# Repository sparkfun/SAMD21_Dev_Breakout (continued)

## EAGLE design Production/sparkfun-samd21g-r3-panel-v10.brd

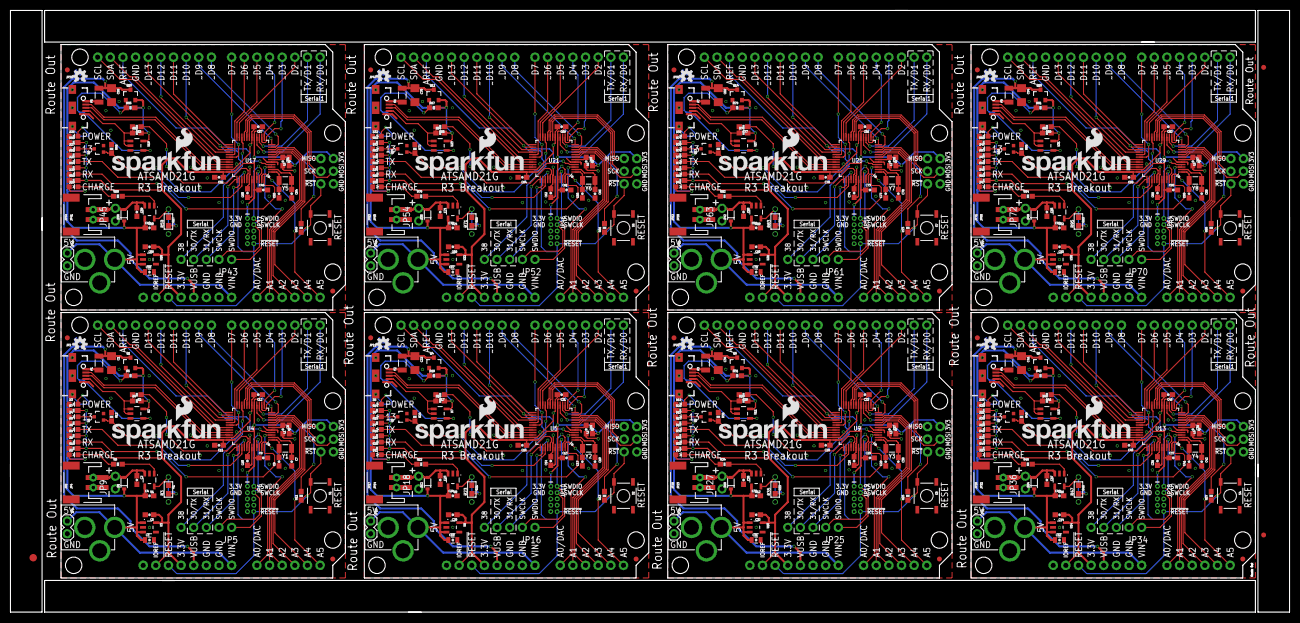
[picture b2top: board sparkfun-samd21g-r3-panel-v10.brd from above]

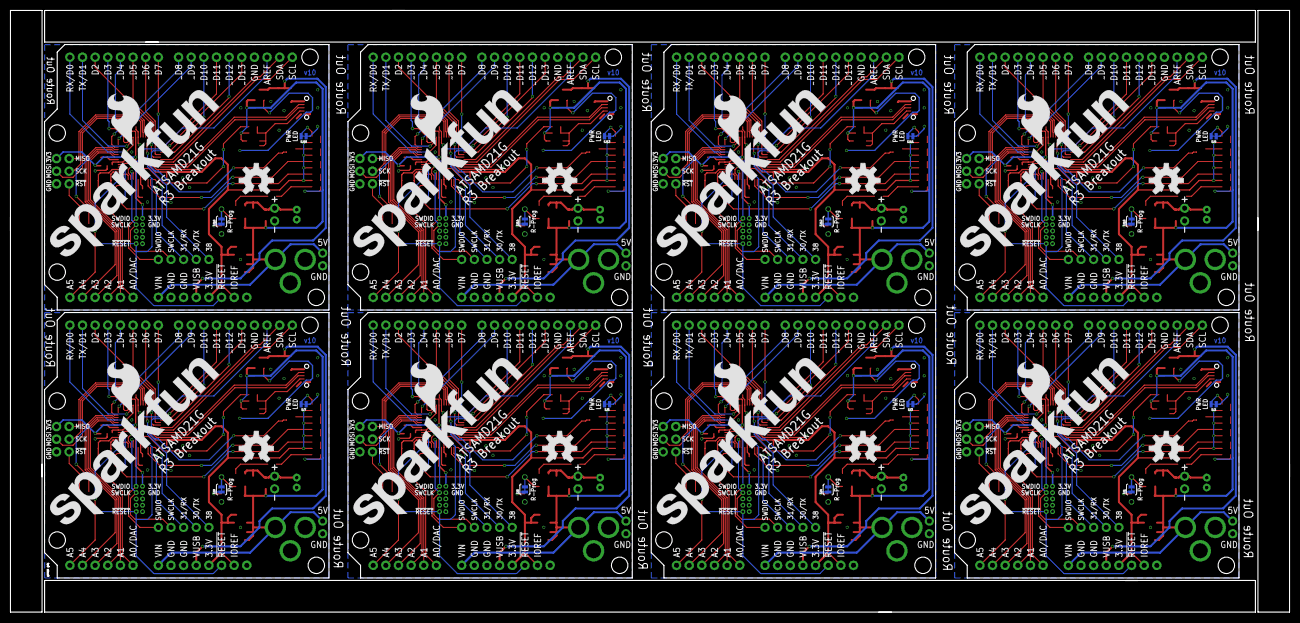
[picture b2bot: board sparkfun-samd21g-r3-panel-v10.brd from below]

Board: 2 copper layers, 257.0 x 120.9 mm, 491 parts (32 on the bottom side), 472 nets.

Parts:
C1, C22, C34, C46, C58, C70, C82, C94: 2.2UF; 1206
C2, C4, C23, C24, C35, C36, C47, C48, C59, C60, C71, C72, C83, C84, C95, C96: 4.7uF; 0603-CAP
C3, C19, C31, C43, C55, C67, C79, C91: 1.0uF; 0805-CAP
C5, C20, C32, C44, C56, C68, C80, C92: 2.2uF; 0603-CAP
C6, C8, C10, C11, C12, C13, C14, C15, C16, C21, C25, C26, C27, C28, C33, C37, C38, C39, C40, C45, C49, C50, C51, C52, C57, C61, C62, C63, C64, C69, C73, C74, C75, C76, C81, C85, C86, C87, C88, C93: 0.1uF; 0603-CAP
C7, C9, C17, C18, C29, C30, C41, C42, C53, C54, C65, C66, C77, C78, C89, C90: 15pF; 0603-CAP
D1, D12, D18, D24, D30, D36, D42, D48: BAT20J; SOD-323
D2, D3, D8, D11, D14, D17, D20, D23, D26, D29, D32, D35, D38, D41, D44, D47: RED; LED-0603
D4, D9, D15, D21, D27, D33, D39, D45: BLUE; LED-0603
D5, D7, D13, D19, D25, D31, D37, D43: GREEN; LED-0603
D6, D10, D16, D22, D28, D34, D40, D46: Yellow; LED-0603
E$1: FIDUCIAL-1.5X3
E$5, E$6: FIDUCIAL-1X2
F1, F2, F3, F4, F5, F6, F7, F8: 500mA; PTC-1206
FID1, FID2, FID3, FID4, FID5, FID6, FID7, FID8, FID9, FID10, FID11, FID12, FID13, FID14, FID15, FID16: FIDUCIAL1X2; FIDUCIAL-1X2
JP1, JP15, JP24, JP33, JP42, JP51, JP60, JP69: 1X02
JP2, JP11, JP20, JP29, JP38, JP47, JP56, JP65: USB-AB-MICRO-SMD_V03
JP3, JP13, JP22, JP31, JP40, JP49, JP58, JP67: POWER_JACKPTH; POWER_JACK_PTH
JP4, JP14, JP23, JP32, JP41, JP50, JP59, JP68: JST-2-SMD
JP5, JP16, JP25, JP34, JP43, JP52, JP61, JP70: 1X05_NO_SILK
JP6, JP10, JP19, JP28, JP37, JP46, JP55, JP64: CORTEX_DEBUGPTH; 2X5-PTH-1.27MM
JP7, JP12, JP21, JP30, JP39, JP48, JP57, JP66: ARDUINO_R3NO_HOLES; ARDUINO_R3_NO_HOLES
JP8, JP17, JP26, JP35, JP44, JP53, JP62, JP71: JST-2-PTH-NS
JP9, JP18, JP27, JP36, JP45, JP54, JP63, JP72: 1X02_NO_SILK
L1, L2, L3, L4, L5, L6, L7, L8: FB - 30Ohm; 0603
LOGO1, LOGO6, LOGO10, LOGO14, LOGO18, LOGO22, LOGO26, LOGO30: SFE_LOGO_NAME_FLAME.2_INCH; SFE_LOGO_NAME_FLAME_.2
LOGO2, LOGO7, LOGO11, LOGO15, LOGO19, LOGO23, LOGO27, LOGO31: SFE_LOGO_NAME_FLAME.4_INCH; SFE_LOGO_NAME_FLAME_.4
LOGO3, LOGO5, LOGO9, LOGO13, LOGO17, LOGO21, LOGO25, LOGO29: OSHW-LOGOS; OSHW-LOGO-S
LOGO4, LOGO8, LOGO12, LOGO16, LOGO20, LOGO24, LOGO28, LOGO32: OSHW-LOGOL; OSHW-LOGO-L
Q1, Q4, Q6, Q8, Q10, Q12, Q14, Q16: 2.5A/30V; SOT23-3
Q2, Q3, Q5, Q7, Q9, Q11, Q13, Q15: 2N7002PW; SOT323
R1, R21, R33, R45, R57, R69, R81, R93: 3.9K; 0603
R2, R6, R7, R8, R9, R10, R14, R15, R17, R18, R20, R22, R26, R27, R29, R30, R32, R34, R38, R39, R41, R42, R44, R46, R50, R51, R53, R54, R56, R58, R62, R63, R65, R66, R68, R70, R74, R75, R77, R78, R80, R82, R86, R87, R89, R90, R92, R94: 330; 0603-RES
R3, R23, R35, R47, R59, R71, R83, R95: PROG; 1/6W-RES
R4, R12, R16, R24, R28, R36, R40, R48, R52, R60, R64, R72, R76, R84, R88, R96: 100k; 0603-RES
R5, R19, R31, R43, R55, R67, R79, R91: 47K; 0603-RES
R11, R13, R25, R37, R49, R61, R73, R85: 10K; 0603-RES
S1, S2, S3, S4, S5, S6, S7, S8: RESET; TACTILE-SWITCH-SMD
SJ1, SJ4, SJ6, SJ8, SJ10, SJ12, SJ14, SJ16: R-prog; PAD-JUMPER-2-NC_BY_TRACE_YES_SILK
SJ2, SJ3, SJ5, SJ7, SJ9, SJ11, SJ13, SJ15: PWR-LED; PAD-JUMPER-2-NC_BY_TRACE_NO_SILK
STANDOFF1, STANDOFF2, STANDOFF3, STANDOFF4, STANDOFF5, STANDOFF6, STANDOFF7, STANDOFF8, STANDOFF9, STANDOFF10, STANDOFF11, STANDOFF12, STANDOFF13, STANDOFF14, STANDOFF15, STANDOFF16, STANDOFF17, STANDOFF18, STANDOFF19, STANDOFF20, STANDOFF21, STANDOFF22, STANDOFF23, STANDOFF24, STANDOFF25, STANDOFF26, STANDOFF27, STANDOFF28, STANDOFF29, STANDOFF30, STANDOFF31, STANDOFF32: STAND-OFF
U1, U8, U12, U16, U20, U24, U28, U32: MCP73831; SOT23-5
U2, U7, U11, U15, U19, U23, U27, U31: 74AHC1G125; SOT23-5
U3, U6, U10, U14, U18, U22, U26, U30: 3.3V; SOT23-5
U4, U5, U9, U13, U17, U21, U25, U29: ATSAMD21G-A; TQFP-48
Y1, Y2, Y3, Y4, Y5, Y6, Y7, Y8: 32.768kHz; CRYSTAL-SMD-3.2X1.5MM

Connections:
3.3V: C5.1, C8.1, C11.1, C12.1, JP6.1, JP7.3.3V, JP7.IOREF, JP7.VCC, L1.1, R7.2, R8.2, R9.2, R10.2, R11.2, U3.5, U4.17, U4.36, U4.44
3.3V1: C13.1, C16.1, C20.1, C21.1, JP10.1, JP12.3.3V, JP12.IOREF, JP12.VCC, L2.1, R13.2, R14.2, R15.2, R18.2, R20.2, U5.17, U5.36, U5.44, U6.5
3.3V2: C25.1, C28.1, C32.1, C33.1, JP19.1, JP21.3.3V, JP21.IOREF, JP21.VCC, L3.1, R25.2, R26.2, R27.2, R30.2, R32.2, U9.17, U9.36, U9.44, U10.5
3.3V3: C37.1, C40.1, C44.1, C45.1, JP28.1, JP30.3.3V, JP30.IOREF, JP30.VCC, L4.1, R37.2, R38.2, R39.2, R42.2, R44.2, U13.17, U13.36, U13.44, U14.5
3.3V4: C49.1, C52.1, C56.1, C57.1, JP37.1, JP39.3.3V, JP39.IOREF, JP39.VCC, L5.1, R49.2, R50.2, R51.2, R54.2, R56.2, U17.17, U17.36, U17.44, U18.5
3.3V5: C61.1, C64.1, C68.1, C69.1, JP46.1, JP48.3.3V, JP48.IOREF, JP48.VCC, L6.1, R61.2, R62.2, R63.2, R66.2, R68.2, U21.17, U21.36, U21.44, U22.5
3.3V6: C73.1, C76.1, C80.1, C81.1, JP55.1, JP57.3.3V, JP57.IOREF, JP57.VCC, L7.1, R73.2, R74.2, R75.2, R78.2, R80.2, U25.17, U25.36, U25.44, U26.5
3.3V7: C85.1, C88.1, C92.1, C93.1, JP64.1, JP66.3.3V, JP66.IOREF, JP66.VCC, L8.1, R85.2, R86.2, R87.2, R90.2, R92.2, U29.17, U29.36, U29.44, U30.5
!RESET: JP6.10, JP7.RESET@1, JP7.RESET@2, R11.1, S1.3, U4.40
!RESET1: JP10.10, JP12.RESET@1, JP12.RESET@2, R13.1, S2.3, U5.40
!RESET2: JP19.10, JP21.RESET@1, JP21.RESET@2, R25.1, S3.3, U9.40
!RESET3: JP28.10, JP30.RESET@1, JP30.RESET@2, R37.1, S4.3, U13.40
!RESET4: JP37.10, JP39.RESET@1, JP39.RESET@2, R49.1, S5.3, U17.40
!RESET5: JP46.10, JP48.RESET@1, JP48.RESET@2, R61.1, S6.3, U21.40
!RESET6: JP55.10, JP57.RESET@1, JP57.RESET@2, R73.1, S7.3, U25.40
!RESET7: JP64.10, JP66.RESET@1, JP66.RESET@2, R85.1, S8.3, U29.40
A0: JP7.A0, U4.3
A1: JP7.A1, U4.7
A2: JP7.A2, U4.8
A3: JP7.A3, U4.9
A4: JP7.A4, U4.10
A5: JP7.A5, U4.47
A6: JP12.A3, U5.9
A7: JP12.A2, U5.8
A8: JP12.A1, U5.7
A9: JP12.A0, U5.3
A10: JP12.A4, U5.10
A11: JP12.A5, U5.47
A12: JP21.A3, U9.9
A13: JP21.A2, U9.8
A14: JP21.A1, U9.7
A15: JP21.A0, U9.3
A16: JP21.A4, U9.10
A17: JP21.A5, U9.47
A18: JP30.A3, U13.9
A19: JP30.A2, U13.8
A20: JP30.A1, U13.7
A21: JP30.A0, U13.3
A22: JP30.A4, U13.10
A23: JP30.A5, U13.47
A24: JP39.A3, U17.9
A25: JP39.A2, U17.8
A26: JP39.A1, U17.7
A27: JP39.A0, U17.3
A28: JP39.A4, U17.10
A29: JP39.A5, U17.47
A30: JP48.A3, U21.9
A31: JP48.A2, U21.8
A32: JP48.A1, U21.7
A33: JP48.A0, U21.3
A34: JP48.A4, U21.10
A35: JP48.A5, U21.47
A36: JP57.A3, U25.9
A37: JP57.A2, U25.8
A38: JP57.A1, U25.7
A39: JP57.A0, U25.3
A40: JP57.A4, U25.10
A41: JP57.A5, U25.47
A42: JP66.A3, U29.9
A43: JP66.A2, U29.8
A44: JP66.A1, U29.7
A45: JP66.A0, U29.3
A46: JP66.A4, U29.10
A47: JP66.A5, U29.47
AREF: JP7.AREF, U4.4
AREF1: JP12.AREF, U5.4
AREF2: JP21.AREF, U9.4
AREF3: JP30.AREF, U13.4
AREF4: JP39.AREF, U17.4
AREF5: JP48.AREF, U21.4
AREF6: JP57.AREF, U25.4
AREF7: JP66.AREF, U29.4
CHG_STAT: R6.2, U1.1
CHG_STAT1: R22.2, U8.1
CHG_STAT2: R34.2, U12.1
CHG_STAT3: R46.2, U16.1
CHG_STAT4: R58.2, U20.1
CHG_STAT5: R70.2, U24.1
CHG_STAT6: R82.2, U28.1
CHG_STAT7: R94.2, U32.1
D0/RXI: JP7.D0, U4.16
D0/RXI1: JP12.D0, U5.16
D0/RXI2: JP21.D0, U9.16
D0/RXI3: JP30.D0, U13.16
D0/RXI4: JP39.D0, U17.16
D0/RXI5: JP48.D0, U21.16
D0/RXI6: JP57.D0, U25.16
D0/RXI7: JP66.D0, U29.16
D1: JP12.D4, U5.13
D1/TXO: JP7.D1, U4.15
D1/TXO1: JP12.D1, U5.15
D1/TXO2: JP21.D1, U9.15
D1/TXO3: JP30.D1, U13.15
D1/TXO4: JP39.D1, U17.15
D1/TXO5: JP48.D1, U21.15
D1/TXO6: JP57.D1, U25.15
D1/TXO7: JP66.D1, U29.15
D2: JP7.D2, U4.23
D3: JP7.D3, U4.14
D4: JP7.D4, U4.13
D5: JP7.D5, U4.24
D6: JP7.D6, U4.29
D7: JP7.D7, U4.30
D8: JP7.D8, U4.11
D9: JP7.D9, U4.12
D10: JP7.D10, U4.27
D11: JP7.D11, U4.25
D12: JP7.D12, U4.28
D13: JP7.D13, Q2.1, R12.2, U4.26
D14: JP12.D3, U5.14
D15: JP12.D2, U5.23
D16: JP12.D5, U5.24
D17: JP12.D6, U5.29
D18: JP12.D7, U5.30
D19: JP12.D8, U5.11
D20: JP12.D9, U5.12
D21: JP12.D12, U5.28
D22: JP12.D11, U5.25
D23: JP12.D10, U5.27
D24: JP12.D13, Q3.1, R24.2, U5.26
D25: JP21.D4, U9.13
D26: JP21.D3, U9.14
D27: JP21.D2, U9.23
D28: JP21.D5, U9.24
D29: JP21.D6, U9.29
D30: JP21.D7, U9.30
D31: JP21.D8, U9.11
D32: JP21.D9, U9.12
D33: JP21.D12, U9.28
D34: JP21.D11, U9.25
D35: JP21.D10, U9.27
D36: JP21.D13, Q5.1, R36.2, U9.26
D37: JP30.D4, U13.13
D38: JP30.D3, U13.14
D39: JP30.D2, U13.23
D40: JP30.D5, U13.24
D41: JP30.D6, U13.29
D42: JP30.D7, U13.30
D43: JP30.D8, U13.11
D44: JP30.D9, U13.12
D45: JP30.D12, U13.28
D46: JP30.D11, U13.25
D47: JP30.D10, U13.27
D48: JP30.D13, Q7.1, R48.2, U13.26
D49: JP39.D4, U17.13
D50: JP39.D3, U17.14
D51: JP39.D2, U17.23
D52: JP39.D5, U17.24
D53: JP39.D6, U17.29
D54: JP39.D7, U17.30
D55: JP39.D8, U17.11
D56: JP39.D9, U17.12
D57: JP39.D12, U17.28
D58: JP39.D11, U17.25
D59: JP39.D10, U17.27
D60: JP39.D13, Q9.1, R60.2, U17.26
D61: JP48.D4, U21.13
D62: JP48.D3, U21.14
D63: JP48.D2, U21.23
D64: JP48.D5, U21.24
D65: JP48.D6, U21.29
D66: JP48.D7, U21.30
D67: JP48.D8, U21.11
D68: JP48.D9, U21.12
D69: JP48.D12, U21.28
D70: JP48.D11, U21.25
D71: JP48.D10, U21.27
D72: JP48.D13, Q11.1, R72.2, U21.26
D73: JP57.D4, U25.13
D74: JP57.D3, U25.14
D75: JP57.D2, U25.23
D76: JP57.D5, U25.24
D77: JP57.D6, U25.29
D78: JP57.D7, U25.30
D79: JP57.D8, U25.11
D80: JP57.D9, U25.12
D81: JP57.D12, U25.28
D82: JP57.D11, U25.25
D83: JP57.D10, U25.27
D84: JP57.D13, Q13.1, R84.2, U25.26
D85: JP66.D4, U29.13
D86: JP66.D3, U29.14
D87: JP66.D2, U29.23
D88: JP66.D5, U29.24
D89: JP66.D6, U29.29
D90: JP66.D7, U29.30
D91: JP66.D8, U29.11
D92: JP66.D9, U29.12
D93: JP66.D12, U29.28
D94: JP66.D11, U29.25
D95: JP66.D10, U29.27
D96: JP66.D13, Q15.1, R96.2, U29.26
GND: C1.2, C2.2, C3.2, C4.2, C5.2, C6.2, C7.2, C8.2, C9.1, C10.2, C11.2, C12.2, JP1.1, JP2.GND1, JP2.SHIELD1, JP2.SHIELD2, JP2.SHIELD3, JP3.GND, JP3.GNDBREAK, JP4.1, JP6.3, JP6.5, JP7.GND@1, JP7.GND@2, JP7.GND@3, JP7.GND@4, JP8.1, JP9.1, Q2.2, R1.1, R3.1, R12.1, S1.1, SJ2.1, U1.2, U2.3, U3.2, U4.5, U4.18, U4.35, U4.42
GND1: C13.2, C14.2, C15.2, C16.2, C17.1, C18.2, C19.2, C20.2, C21.2, C22.2, C23.2, C24.2, JP10.3, JP10.5, JP11.GND1, JP11.SHIELD1, JP11.SHIELD2, JP11.SHIELD3, JP12.GND@1, JP12.GND@2, JP12.GND@3, JP12.GND@4, JP13.GND, JP13.GNDBREAK, JP14.1, JP15.1, JP17.1, JP18.1, Q3.2, R21.1, R23.1, R24.1, S2.1, SJ3.1, U5.5, U5.18, U5.35, U5.42, U6.2, U7.3, U8.2
GND2: C25.2, C26.2, C27.2, C28.2, C29.1, C30.2, C31.2, C32.2, C33.2, C34.2, C35.2, C36.2, JP19.3, JP19.5, JP20.GND1, JP20.SHIELD1, JP20.SHIELD2, JP20.SHIELD3, JP21.GND@1, JP21.GND@2, JP21.GND@3, JP21.GND@4, JP22.GND, JP22.GNDBREAK, JP23.1, JP24.1, JP26.1, JP27.1, Q5.2, R33.1, R35.1, R36.1, S3.1, SJ5.1, U9.5, U9.18, U9.35, U9.42, U10.2, U11.3, U12.2
GND3: C37.2, C38.2, C39.2, C40.2, C41.1, C42.2, C43.2, C44.2, C45.2, C46.2, C47.2, C48.2, JP28.3, JP28.5, JP29.GND1, JP29.SHIELD1, JP29.SHIELD2, JP29.SHIELD3, JP30.GND@1, JP30.GND@2, JP30.GND@3, JP30.GND@4, JP31.GND, JP31.GNDBREAK, JP32.1, JP33.1, JP35.1, JP36.1, Q7.2, R45.1, R47.1, R48.1, S4.1, SJ7.1, U13.5, U13.18, U13.35, U13.42, U14.2, U15.3, U16.2
GND4: C49.2, C50.2, C51.2, C52.2, C53.1, C54.2, C55.2, C56.2, C57.2, C58.2, C59.2, C60.2, JP37.3, JP37.5, JP38.GND1, JP38.SHIELD1, JP38.SHIELD2, JP38.SHIELD3, JP39.GND@1, JP39.GND@2, JP39.GND@3, JP39.GND@4, JP40.GND, JP40.GNDBREAK, JP41.1, JP42.1, JP44.1, JP45.1, Q9.2, R57.1, R59.1, R60.1, S5.1, SJ9.1, U17.5, U17.18, U17.35, U17.42, U18.2, U19.3, U20.2
GND5: C61.2, C62.2, C63.2, C64.2, C65.1, C66.2, C67.2, C68.2, C69.2, C70.2, C71.2, C72.2, JP46.3, JP46.5, JP47.GND1, JP47.SHIELD1, JP47.SHIELD2, JP47.SHIELD3, JP48.GND@1, JP48.GND@2, JP48.GND@3, JP48.GND@4, JP49.GND, JP49.GNDBREAK, JP50.1, JP51.1, JP53.1, JP54.1, Q11.2, R69.1, R71.1, R72.1, S6.1, SJ11.1, U21.5, U21.18, U21.35, U21.42, U22.2, U23.3, U24.2
GND6: C73.2, C74.2, C75.2, C76.2, C77.1, C78.2, C79.2, C80.2, C81.2, C82.2, C83.2, C84.2, JP55.3, JP55.5, JP56.GND1, JP56.SHIELD1, JP56.SHIELD2, JP56.SHIELD3, JP57.GND@1, JP57.GND@2, JP57.GND@3, JP57.GND@4, JP58.GND, JP58.GNDBREAK, JP59.1, JP60.1, JP62.1, JP63.1, Q13.2, R81.1, R83.1, R84.1, S7.1, SJ13.1, U25.5, U25.18, U25.35, U25.42, U26.2, U27.3, U28.2
GND7: C85.2, C86.2, C87.2, C88.2, C89.1, C90.2, C91.2, C92.2, C93.2, C94.2, C95.2, C96.2, JP64.3, JP64.5, JP65.GND1, JP65.SHIELD1, JP65.SHIELD2, JP65.SHIELD3, JP66.GND@1, JP66.GND@2, JP66.GND@3, JP66.GND@4, JP67.GND, JP67.GNDBREAK, JP68.1, JP69.1, JP71.1, JP72.1, Q15.2, R93.1, R95.1, R96.1, S8.1, SJ15.1, U29.5, U29.18, U29.35, U29.42, U30.2, U31.3, U32.2
unnamed: F1.1, JP2.VBUS1
unnamed: C9.2, U4.1, Y1.P$2
unnamed: D4.C, Q2.3
unnamed: C7.1, U4.2, Y1.P$1
unnamed: D3.A, R7.1
unnamed: D4.A, R8.1
unnamed: C17.2, U5.1, Y2.P$2
unnamed: D2.C, R6.1
unnamed: C18.1, U5.2, Y2.P$1
unnamed: D5.A, R9.1
unnamed: D6.A, R10.1
unnamed: D3.C, SJ2.2
unnamed: R1.2, SJ1.1
unnamed: D8.A, R14.1
unnamed: R3.2, SJ1.2, U1.5
unnamed: D9.A, R15.1
unnamed: D9.C, Q3.3
unnamed: F2.1, JP11.VBUS1
unnamed: D7.A, R18.1
unnamed: D10.A, R20.1
unnamed: D8.C, SJ3.2
unnamed: R21.2, SJ4.1
unnamed: R23.2, SJ4.2, U8.5
unnamed: D11.C, R22.1
unnamed: C29.2, U9.1, Y3.P$2
unnamed: C30.1, U9.2, Y3.P$1
unnamed: D14.A, R26.1
unnamed: D15.A, R27.1
unnamed: D15.C, Q5.3
unnamed: F3.1, JP20.VBUS1
unnamed: D13.A, R30.1
unnamed: D16.A, R32.1
unnamed: D14.C, SJ5.2
unnamed: R33.2, SJ6.1
unnamed: R35.2, SJ6.2, U12.5
unnamed: D17.C, R34.1
unnamed: C41.2, U13.1, Y4.P$2
unnamed: C42.1, U13.2, Y4.P$1
unnamed: D20.A, R38.1
unnamed: D21.A, R39.1
unnamed: D21.C, Q7.3
unnamed: F4.1, JP29.VBUS1
unnamed: D19.A, R42.1
unnamed: D22.A, R44.1
unnamed: D20.C, SJ7.2
unnamed: R45.2, SJ8.1
unnamed: R47.2, SJ8.2, U16.5
unnamed: D23.C, R46.1
unnamed: C53.2, U17.1, Y5.P$2
unnamed: C54.1, U17.2, Y5.P$1
unnamed: D26.A, R50.1
unnamed: D27.A, R51.1
unnamed: D27.C, Q9.3
unnamed: F5.1, JP38.VBUS1
unnamed: D25.A, R54.1
unnamed: D28.A, R56.1
unnamed: D26.C, SJ9.2
unnamed: R57.2, SJ10.1
unnamed: R59.2, SJ10.2, U20.5
unnamed: D29.C, R58.1
unnamed: C65.2, U21.1, Y6.P$2
unnamed: C66.1, U21.2, Y6.P$1
unnamed: D32.A, R62.1
unnamed: D33.A, R63.1
unnamed: D33.C, Q11.3
unnamed: F6.1, JP47.VBUS1
unnamed: D31.A, R66.1
unnamed: D34.A, R68.1
unnamed: D32.C, SJ11.2
unnamed: R69.2, SJ12.1
unnamed: R71.2, SJ12.2, U24.5
unnamed: D35.C, R70.1
unnamed: C77.2, U25.1, Y7.P$2
unnamed: C78.1, U25.2, Y7.P$1
unnamed: D38.A, R74.1
unnamed: D39.A, R75.1
unnamed: D39.C, Q13.3
unnamed: F7.1, JP56.VBUS1
unnamed: D37.A, R78.1
unnamed: D40.A, R80.1
unnamed: D38.C, SJ13.2
unnamed: R81.2, SJ14.1
unnamed: R83.2, SJ14.2, U28.5
unnamed: D41.C, R82.1
unnamed: C89.2, U29.1, Y8.P$2
unnamed: C90.1, U29.2, Y8.P$1
unnamed: D44.A, R86.1
unnamed: D45.A, R87.1
unnamed: D45.C, Q15.3
unnamed: F8.1, JP65.VBUS1
unnamed: D43.A, R90.1
unnamed: D46.A, R92.1
unnamed: D44.C, SJ15.2
unnamed: R93.2, SJ16.1
unnamed: R95.2, SJ16.2, U32.5
unnamed: D47.C, R94.1
PA1: JP16.5, U5.22
PA2: JP25.5, U9.22
PA3: JP34.5, U13.22
PA4: JP43.5, U17.22
PA5: JP52.5, U21.22
PA6: JP61.5, U25.22
PA7: JP70.5, U29.22
PA13: JP5.5, U4.22
PB1: JP16.4, U5.37
PB2: JP16.3, U5.38
PB3: JP25.4, U9.37
PB4: JP25.3, U9.38
PB5: JP34.4, U13.37
PB6: JP34.3, U13.38
PB7: JP43.4, U17.37
PB8: JP43.3, U17.38
PB9: JP52.4, U21.37
PB10: JP52.3, U21.38
PB11: JP61.4, U25.37
PB12: JP61.3, U25.38
PB13: JP70.4, U29.37
PB14: JP70.3, U29.38
PB22: JP5.4, U4.37
PB23: JP5.3, U4.38
RX_LED: D6.C, U4.48
RX_LED1: D10.C, U5.48
RX_LED2: D16.C, U9.48
RX_LED3: D22.C, U13.48
RX_LED4: D28.C, U17.48
RX_LED5: D34.C, U21.48
RX_LED6: D40.C, U25.48
RX_LED7: D46.C, U29.48
SCL: JP7.SCL, U4.32
SCL1: JP12.SCL, U5.32
SCL2: JP21.SCL, U9.32
SCL3: JP30.SCL, U13.32
SCL4: JP39.SCL, U17.32
SCL5: JP48.SCL, U21.32
SCL6: JP57.SCL, U25.32
SCL7: JP66.SCL, U29.32
SDA: JP7.SDA, U4.31
SDA1: JP12.SDA, U5.31
SDA2: JP21.SDA, U9.31
SDA3: JP30.SDA, U13.31
SDA4: JP39.SDA, U17.31
SDA5: JP48.SDA, U21.31
SDA6: JP57.SDA, U25.31
SDA7: JP66.SDA, U29.31
SPI_MISO: JP7.MISO, U4.21
SPI_MISO1: JP12.MISO, U5.21
SPI_MISO2: JP21.MISO, U9.21
SPI_MISO3: JP30.MISO, U13.21
SPI_MISO4: JP39.MISO, U17.21
SPI_MISO5: JP48.MISO, U21.21
SPI_MISO6: JP57.MISO, U25.21
SPI_MISO7: JP66.MISO, U29.21
SPI_MOSI: JP7.MOSI, U4.19
SPI_MOSI1: JP12.MOSI, U5.19
SPI_MOSI2: JP21.MOSI, U9.19
SPI_MOSI3: JP30.MOSI, U13.19
SPI_MOSI4: JP39.MOSI, U17.19
SPI_MOSI5: JP48.MOSI, U21.19
SPI_MOSI6: JP57.MOSI, U25.19
SPI_MOSI7: JP66.MOSI, U29.19
SPI_SCK: JP7.SCK, U4.20
SPI_SCK1: JP12.SCK, U5.20
SPI_SCK2: JP21.SCK, U9.20
SPI_SCK3: JP30.SCK, U13.20
SPI_SCK4: JP39.SCK, U17.20
SPI_SCK5: JP48.SCK, U21.20
SPI_SCK6: JP57.SCK, U25.20
SPI_SCK7: JP66.SCK, U29.20
SWCLK: JP5.2, JP6.4, U4.45
SWCLK1: JP10.4, JP16.2, U5.45
SWCLK2: JP19.4, JP25.2, U9.45
SWCLK3: JP28.4, JP34.2, U13.45
SWCLK4: JP37.4, JP43.2, U17.45
SWCLK5: JP46.4, JP52.2, U21.45
SWCLK6: JP55.4, JP61.2, U25.45
SWCLK7: JP64.4, JP70.2, U29.45
SWDIO: JP5.1, JP6.2, U4.46
SWDIO1: JP10.2, JP16.1, U5.46
SWDIO2: JP19.2, JP25.1, U9.46
SWDIO3: JP28.2, JP34.1, U13.46
SWDIO4: JP37.2, JP43.1, U17.46
SWDIO5: JP46.2, JP52.1, U21.46
SWDIO6: JP55.2, JP61.1, U25.46
SWDIO7: JP64.2, JP70.1, U29.46
TX_LED: D5.C, U4.39
TX_LED1: D7.C, U5.39
TX_LED2: D13.C, U9.39
TX_LED3: D19.C, U13.39
TX_LED4: D25.C, U17.39
TX_LED5: D31.C, U21.39
TX_LED6: D37.C, U25.39
TX_LED7: D43.C, U29.39
USB_D+: JP2.D+1, U4.34
USB_D+1: JP11.D+1, U5.34
USB_D+2: JP20.D+1, U9.34
USB_D+3: JP29.D+1, U13.34
USB_D+4: JP38.D+1, U17.34
USB_D+5: JP47.D+1, U21.34
USB_D+6: JP56.D+1, U25.34
USB_D+7: JP65.D+1, U29.34
USB_D-: JP2.D-1, U4.33
USB_D-1: JP11.D-1, U5.33
USB_D-2: JP20.D-1, U9.33
USB_D-3: JP29.D-1, U13.33
USB_D-4: JP38.D-1, U17.33
USB_D-5: JP47.D-1, U21.33
USB_D-6: JP56.D-1, U25.33
USB_D-7: JP65.D-1, U29.33
USB_HOST_EN: R2.1, U4.41
USB_HOST_EN1: R17.1, U5.41
USB_HOST_EN2: R29.1, U9.41
USB_HOST_EN3: R41.1, U13.41
USB_HOST_EN4: R53.1, U17.41
USB_HOST_EN5: R65.1, U21.41
USB_HOST_EN6: R77.1, U25.41
USB_HOST_EN7: R89.1, U29.41
USB_HOST_POWER_EN: Q1.1, R5.1, U2.4
USB_HOST_POWER_EN1: Q4.1, R19.1, U7.4
USB_HOST_POWER_EN2: Q6.1, R31.1, U11.4
USB_HOST_POWER_EN3: Q8.1, R43.1, U15.4
USB_HOST_POWER_EN4: Q10.1, R55.1, U19.4
USB_HOST_POWER_EN5: Q12.1, R67.1, U23.4
USB_HOST_POWER_EN6: Q14.1, R79.1, U27.4
USB_HOST_POWER_EN7: Q16.1, R91.1, U31.4
USB_ID: JP2.ID1, R2.2, R4.1, U2.1, U2.2
USB_ID1: JP11.ID1, R16.1, R17.2, U7.1, U7.2
USB_ID2: JP20.ID1, R28.1, R29.2, U11.1, U11.2
USB_ID3: JP29.ID1, R40.1, R41.2, U15.1, U15.2
USB_ID4: JP38.ID1, R52.1, R53.2, U19.1, U19.2
USB_ID5: JP47.ID1, R64.1, R65.2, U23.1, U23.2
USB_ID6: JP56.ID1, R76.1, R77.2, U27.1, U27.2
USB_ID7: JP65.ID1, R88.1, R89.2, U31.1, U31.2
VBAT: C2.1, D1.A, JP4.2, JP8.2, JP9.2, U1.3
VBAT1: C23.1, D12.A, JP14.2, JP17.2, JP18.2, U8.3
VBAT2: C35.1, D18.A, JP23.2, JP26.2, JP27.2, U12.3
VBAT3: C47.1, D24.A, JP32.2, JP35.2, JP36.2, U16.3
VBAT4: C59.1, D30.A, JP41.2, JP44.2, JP45.2, U20.3
VBAT5: C71.1, D36.A, JP50.2, JP53.2, JP54.2, U24.3
VBAT6: C83.1, D42.A, JP59.2, JP62.2, JP63.2, U28.3
VBAT7: C95.1, D48.A, JP68.2, JP71.2, JP72.2, U32.3
VDDANA: C6.1, L1.2, U4.6
VDDANA1: C15.1, L2.2, U5.6
VDDANA2: C27.1, L3.2, U9.6
VDDANA3: C39.1, L4.2, U13.6
VDDANA4: C51.1, L5.2, U17.6
VDDANA5: C63.1, L6.2, U21.6
VDDANA6: C75.1, L7.2, U25.6
VDDANA7: C87.1, L8.2, U29.6
VDDCORE: C10.1, U4.43
VDDCORE1: C14.1, U5.43
VDDCORE2: C26.1, U9.43
VDDCORE3: C38.1, U13.43
VDDCORE4: C50.1, U17.43
VDDCORE5: C62.1, U21.43
VDDCORE6: C74.1, U25.43
VDDCORE7: C86.1, U29.43
VIN: C3.1, C4.1, D1.C, D2.A, JP1.2, JP3.PWR, JP7.VIN, Q1.2, R4.2, R5.2, U1.4, U2.5, U3.1, U3.3
VIN1: C19.1, C24.1, D11.A, D12.C, JP12.VIN, JP13.PWR, JP15.2, Q4.2, R16.2, R19.2, U6.1, U6.3, U7.5, U8.4
VIN2: C31.1, C36.1, D17.A, D18.C, JP21.VIN, JP22.PWR, JP24.2, Q6.2, R28.2, R31.2, U10.1, U10.3, U11.5, U12.4
VIN3: C43.1, C48.1, D23.A, D24.C, JP30.VIN, JP31.PWR, JP33.2, Q8.2, R40.2, R43.2, U14.1, U14.3, U15.5, U16.4
VIN4: C55.1, C60.1, D29.A, D30.C, JP39.VIN, JP40.PWR, JP42.2, Q10.2, R52.2, R55.2, U18.1, U18.3, U19.5, U20.4
VIN5: C67.1, C72.1, D35.A, D36.C, JP48.VIN, JP49.PWR, JP51.2, Q12.2, R64.2, R67.2, U22.1, U22.3, U23.5, U24.4
VIN6: C79.1, C84.1, D41.A, D42.C, JP57.VIN, JP58.PWR, JP60.2, Q14.2, R76.2, R79.2, U26.1, U26.3, U27.5, U28.4
VIN7: C91.1, C96.1, D47.A, D48.C, JP66.VIN, JP67.PWR, JP69.2, Q16.2, R88.2, R91.2, U30.1, U30.3, U31.5, U32.4
VUSB: C1.1, F1.2, JP7.5V, Q1.3
VUSB1: C22.1, F2.2, JP12.5V, Q4.3
VUSB2: C34.1, F3.2, JP21.5V, Q6.3
VUSB3: C46.1, F4.2, JP30.5V, Q8.3
VUSB4: C58.1, F5.2, JP39.5V, Q10.3
VUSB5: C70.1, F6.2, JP48.5V, Q12.3
VUSB6: C82.1, F7.2, JP57.5V, Q14.3
VUSB7: C94.1, F8.2, JP66.5V, Q16.3

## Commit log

2015-06-09 Initial commit of PCB layout.
2015-06-09 Minor fixes for pre-QC check.
2015-06-10 Adding SMD JST package, moving LEDs and USB to accomodate.
2015-06-10 Renaming files and board name silk.
2015-06-10 Re-routing some traces to increase ground pour.
2015-06-15 Adding PROD_ID to L1.
2015-09-28 Swapping D2 and D4.
2015-09-28 Moving Cortex-M0 programming header down 0.025"
2015-09-28 Adding pull-down resistor to D13 LED/MOSFET
2015-09-28 Upping version number to v10
2015-09-28 Pulling buffer up to VIN instead of 3.3V
2015-09-28 Swapping MIC5205 Regulator out for AP2112K-3.3V
2015-09-28 Adding pin numbers to middle-board pins. Adding PWM indicators.
2015-09-29 Tweaking schematic and layout silk for checklist
2015-09-30 Adding silk to detail serial ports and DAC pin
2015-09-30 One last little silk clean up
2015-10-07 created panel v10
2015-10-29 Fixing typo in comment about SJ1.
2015-11-12 Revising file name to match product name.
2015-11-12 Adding version 1.0 of the schematic.
2015-11-12 Adding graphical datasheets.
2015-11-12 Big readme update.
2015-11-12 Fixing link error in readme.
2015-11-16 Adding SAM_BA SAMD21 bootloader
2015-12-07 Adding license
2019-02-21 Adds UF2 binary and arduino sketch update bootloader as well as just the bootloader.
    * Adds readme explaining UF2 bootloaders and Circuit Python
    * Adds Circuit Python UF2 file
